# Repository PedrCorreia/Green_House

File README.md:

# LoRaWAN Greenhouse Environmental Monitoring System

**Group 34346** — DTU IoT Project

Distributed IoT system for real-time greenhouse environmental monitoring using LoRa/LoRaWAN wireless communication over ESP32-based sensor nodes.

**Languages & Technologies:** C/C++ | Python | JavaScript | KiCad | Arduino

---

## System Overview

Multi-node greenhouse monitoring network with dual LoRa communication paths.

### Node Architecture
```
5 ESP32-based Nodes:
  • Sensor Node (LoRa P2P telemetry)
  • LoRaWAN Sensor Node (Cibicom OTAA uplink)
  • Gateway (WiFi/MQTT bridge + LoRa P2P RX)
  • Gateway Slave (LoRaWAN serial bridge)
  • Light Control Node (LoRa P2P receiver)
```

### Monitored Parameters
| Parameter | Sensor | Range |
|-----------|--------|-------|
| Temperature & Humidity | DHT22 | -40…+85°C, 0-100% |
| Soil Moisture | Capacitive | 0-100% |
| Light Intensity | KY-018 | 0-4095 lux |
| Battery Voltage | ADC | 0-5000 mV |

### Technology Stack
| Component | Technology |
|-----------|------------|
| Microcontroller | ESP32 DevKit V1 |
| Radio Module | RN2483 LoRa |
| Power Management | AP2112K-3.3 LDO, AO3401A MOSFET |
| PCB Design | KiCad 10.0.0 |
| Communications | LoRa P2P, LoRaWAN (OTAA), WiFi, MQTT |

---

## Firmware Targets

| Target | Language | File | Purpose |
|--------|----------|------|---------|
| Sensor Node | C++ | sensor-node.ino | DHT22/soil/light telemetry over LoRa P2P |
| LoRaWAN Sensor | C++ | lorawan-sensor-node.cpp | OTAA uplink to Cibicom/Loriot |
| Gateway | C++ | gateway.cpp | WiFi/MQTT bridge, LoRa P2P receiver |
| Gateway Slave | C++ | gateway-slave.cpp | LoRaWAN serial bridge |
| Light Node | C++ | light-node.ino | LoRa P2P command receiver for LED control |
| Backend Router | Python | loriot_router.py | 

---

## Communication Architecture

### Primary Path (LoRa P2P)
```
Sensor Node ──LoRa P2P──→ Gateway ──WiFi──→ MQTT Broker ──JSON──→ Dashboard
```

### Secondary Path (LoRaWAN)
```
LoRaWAN Sensor ──LoRaWAN──→ Cibicom/Loriot ──Webhook──→ Router ──MQTT──→ Dashboard
```
---

## Documentation

Individual README files in each directory contain hardware pinouts, configuration details, testing procedures, and troubleshooting.

**References:**
- [RN2483 Datasheet](https://ww1.microchip.com/downloads/en/DeviceDoc/40001811G.pdf)
- [ESP32 Arduino Core](https://github.com/espressif/arduino-esp32)
- [Cibicom LoRaWAN](https://iotnet.teracom.dk)
- [MQTT Protocol](https://mqtt.org)
- [Communication Flowchart](COMMUNICATION_FLOWCHART.md)
- [Hardware Schematics](hardware/)
- [Test Results](test/README.md)

---

**Last Updated:** May 2026 | **Status:** Ready for Submission | **Contact:** Group 34346

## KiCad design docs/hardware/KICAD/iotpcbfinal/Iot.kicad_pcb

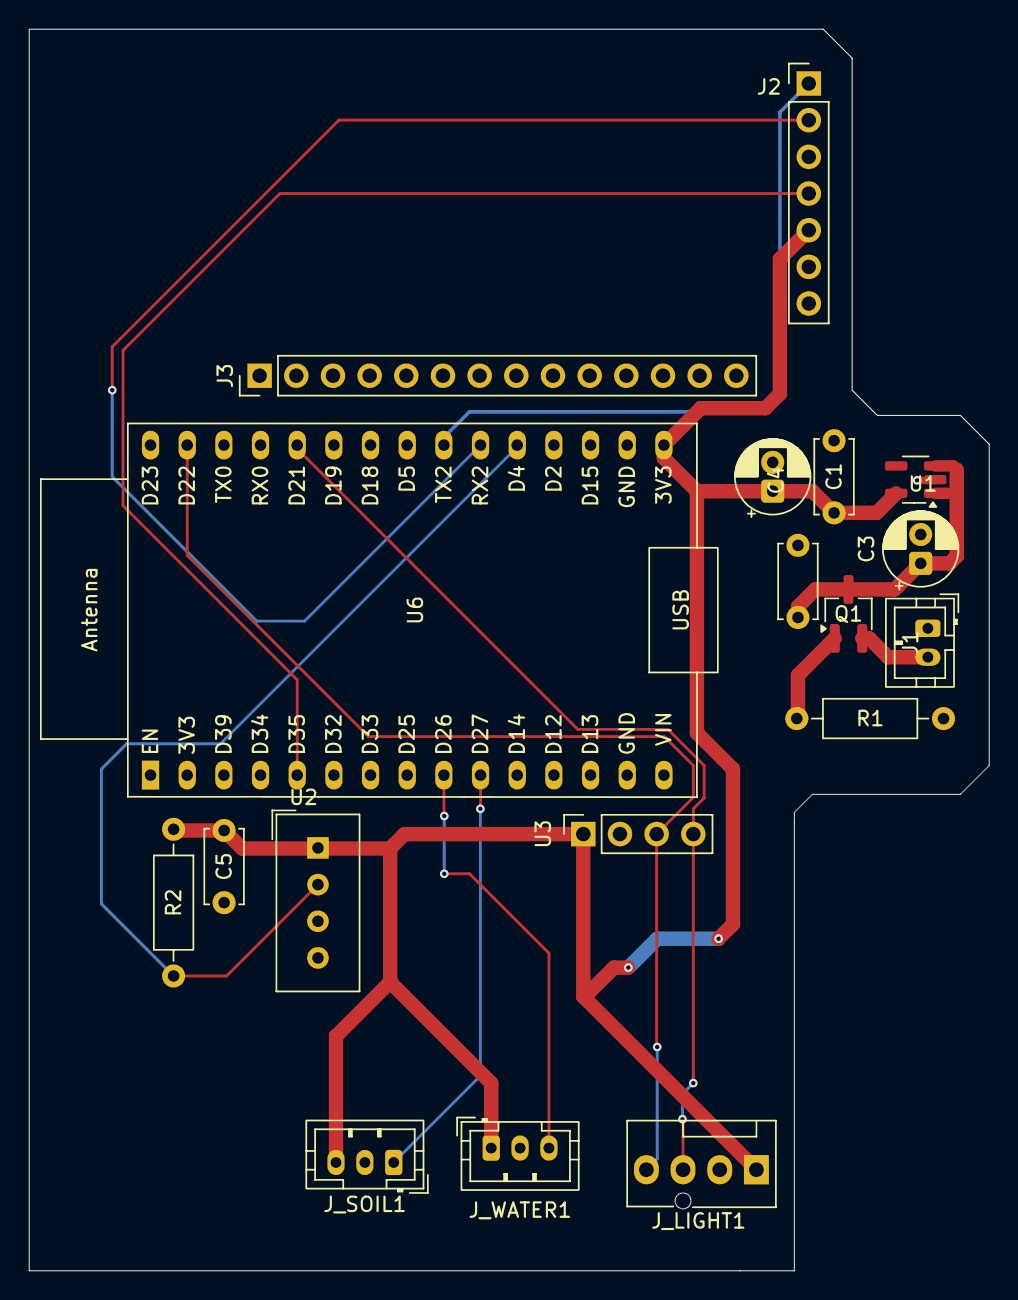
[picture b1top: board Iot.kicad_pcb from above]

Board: 2 copper layers, 66.5 x 86.0 mm, 18 parts (0 on the bottom side), 13 nets.

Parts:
C1, C2: 10uF; C_Disc_D5.0mm_W2.5mm_P5.00mm
C3, C4: 100uF; CP_Radial_D5.0mm_P2.00mm
C5: 100nF; C_Disc_D5.0mm_W2.5mm_P5.00mm
J1: Conn_01x02_Socket; JST_PH_B2B-PH-K_1x02_P2.00mm_Vertical
J2: Conn_01x07_Socket; PinHeader_1x07_P2.54mm_Vertical
J3: Conn_01x14_Socket; PinHeader_1x14_P2.54mm_Vertical
J_LIGHT1: Conn_01x04_Socket; FanPinHeader_1x04_P2.54mm_Vertical
J_SOIL1: Conn_01x03_Socket; JST_PH_B3B-PH-K_1x03_P2.00mm_Vertical
J_WATER1: Conn_01x03_Socket; JST_PH_B3B-PH-K_1x03_P2.00mm_Vertical
Q1: AO3401A; SOT-23W_Handsoldering
R1: 10kΩ; R_Axial_DIN0207_L6.3mm_D2.5mm_P10.16mm_Horizontal
R2: 4.7kΩ; R_Axial_DIN0207_L6.3mm_D2.5mm_P10.16mm_Horizontal
U1: AP2112K-3.3; SOT-23-5_HandSoldering
U2: DHT11; Aosong_DHT11_5.5x12.0_P2.54mm
U3: ER_OLEDM0.91_1x-I2C; PinSocket_1x04_P2.54mm_Vertical
U6: ESP32-C3-DevKitC-02

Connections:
/4.7VIN: J1.2, Q1.2 (S)
/+3V3: C1.1, C4.1, C5.1, J2.5, J_LIGHT1.1, J_SOIL1.3, J_WATER1.1, R2.1, U1.5 (VOUT), U2.1 (VDD), U3.2 (VCC), U6.16 (3.3v)
/I2C_SCL: J_LIGHT1.4, U3.3 (SCL), U6.29 (GPIO22)
/I2C_SDA: J_LIGHT1.3, U3.4 (SDA), U6.26 (GPIO21)
/LORA_RST: J2.4, U6.5 (GPIO14)
/LORA_RX: J2.1, U6.22 (GPIO17)
/LORA_TX: J2.2, U6.21 (GPIO16)
/SOIL_MOIST: J_SOIL1.1, U6.10 (GPIO32)
/TH: R2.2, U2.2 (DATA), U6.20 (GPIO4)
/WATER_LEAK: J_WATER1.3, U6.9 (GPIO33)
Earth: C1.2, C2.2, C3.2, C4.2, C5.2, J1.1, J2.7, J_LIGHT1.2, J_SOIL1.2, J_WATER1.2, R1.2, U1.2 (GND), U2.4 (GND), U3.1 (GND), U6.17 (GND)
unnamed: C2.1, C3.1, Q1.3 (D), U1.1 (VIN), U1.3 (EN)
unnamed: Q1.1 (G), R1.1

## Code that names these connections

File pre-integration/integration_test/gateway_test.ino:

#include <Arduino.h>
#include <HardwareSerial.h>
#include <Wire.h>
#include <Adafruit_GFX.h>
#include <Adafruit_SH110X.h>

// --- LoRa Pins (Matching your Gateway) ---
#define LORA_UART_RX_PIN 16    // ESP32 GPIO16 -> RN2483 TX
#define LORA_UART_TX_PIN 17    // ESP32 GPIO17 -> RN2483 RX
#define RN2483_RST_PIN   2

// --- Display Pins ---
#define I2C_SDA 21
#define I2C_SCL 22

// --- LoRa Settings ---
#define LORA_BAUD_RATE   57600UL
#define LORA_FREQ        868100000UL
#define LORA_PWR         14
#define LORA_SF          "sf12"

// --- Hardware Objects ---
HardwareSerial loraSerial(2);

#define SCREEN_WIDTH 128
#define SCREEN_HEIGHT 64
#define OLED_RESET -1
Adafruit_SH1106G display = Adafruit_SH1106G(SCREEN_WIDTH, SCREEN_HEIGHT, &Wire, OLED_RESET);
bool oled_connected = false;

// Variables to track last received data
String lastRxHex = "";
uint32_t lastId = 0;
float lastTemp = 0.0;
uint8_t lastHum = 0;
uint16_t lastLux = 0;
uint16_t lastSoil = 0;
unsigned long lastRxTime = 0;
int lastRssi = 0; // Signal strength (dBm)

int hexNibble(char c) {
  if (c >= '0' && c <= '9') return c - '0';
  if (c >= 'A' && c <= 'F') return c - 'A' + 10;
  if (c >= 'a' && c <= 'f') return c - 'a' + 10;
  return -1;
}

bool hexToBytes(const String& hexStr, uint8_t* out, size_t outLen) {
  if (hexStr.length() != outLen * 2) return false;
  for (size_t i = 0; i < outLen; i++) {
    int hi = hexNibble(hexStr.charAt(i * 2));
    int lo = hexNibble(hexStr.charAt(i * 2 + 1));
    if (hi < 0 || lo < 0) return false;
    out[i] = (uint8_t)((hi << 4) | lo);
  }
  return true;
}

void parsePayload(String hexStr) {
  if (hexStr.length() != 26) {
    Serial.println("Invalid payload length!");
    return;
  }

  uint8_t b[13];
  if (!hexToBytes(hexStr, b, sizeof(b))) {
    Serial.println("Invalid hex string!");
    return;
  }

  // Parse ID
  lastId = ((uint32_t)b[0] << 24) | ((uint32_t)b[1] << 16) | ((uint32_t)b[2] << 8) | b[3];
  
  // Parse Temp (tenths of C)
  int16_t tempRaw = (int16_t)((b[4] << 8) | b[5]);
  lastTemp = tempRaw / 10.0;

  // Parse Humidity
  lastHum = b[6];

  // Parse Lux
  lastLux = (uint16_t)((b[7] << 8) | b[8]);

  // Parse Soil
  lastSoil = (uint16_t)((b[9] << 8) | b[10]);

  lastRxTime = millis();
}

void updateUI() {
  if (!oled_connected) return;
  display.clearDisplay();
  
  display.setTextSize(1);
  display.setCursor(0, 0);
  display.print("TEST GATEWAY RX");
  display.drawLine(0, 10, 128, 10, SH110X_WHITE);

  if (lastRxTime == 0) {
    display.setCursor(0, 25);
    display.println("Waiting for LoRa...");
  } else {
    display.setCursor(0, 15);
    display.printf("Node ID: %08X", lastId);
    
    display.setCursor(0, 28);
    display.printf("T:%.1fC  H:%d%%", lastTemp, lastHum);
    
    display.setCursor(0, 41);
    display.printf("RSSI: %d dBm", lastRssi);

    // Time since last RX
    unsigned long secAgo = (millis() - lastRxTime) / 1000;
    display.setCursor(0, 54);
    display.printf("Last RX: %ds ago", secAgo);
  }
  
  display.display();
}

void setup() {
  Serial.begin(115200);
  delay(1000);
  Serial.println("\n--- Integration Test: Gateway RX ---");

  // OLED Init
  Wire.begin(I2C_SDA, I2C_SCL);
  if(!display.begin(0x3C, true) && !display.begin(0x3D, true)) {
    Serial.println("WARNING: OLED not found");
  } else {
    oled_connected = true;
    display.clearDisplay();
    display.setTextColor(SH110X_WHITE);
    updateUI();
  }

  // LoRa Init
  pinMode(RN2483_RST_PIN, OUTPUT);
  loraSerial.begin(LORA_BAUD_RATE, SERIAL_8N1, LORA_UART_RX_PIN, LORA_UART_TX_PIN);
  loraSerial.setTimeout(1000);
  
  digitalWrite(RN2483_RST_PIN, LOW);
  delay(200);
  digitalWrite(RN2483_RST_PIN, HIGH);
  delay(500);

  while (loraSerial.available()) loraSerial.read();
  
  loraSerial.print("sys get ver\r\n");
  String ver = loraSerial.readStringUntil('\n');
  ver.trim();
  if (ver.length() > 0) {
    Serial.print("RN2483 Ready: ");
    Serial.println(ver);

    loraSerial.print("mac pause\r\n"); delay(50);
    loraSerial.print("radio set mod lora\r\n"); delay(50);
    loraSerial.print("radio set freq 868100000\r\n"); delay(50);
    loraSerial.print("radio set pwr 14\r\n"); delay(50);
    loraSerial.print("radio set sf sf12\r\n"); delay(50);
    loraSerial.print("radio set afcbw 41.7\r\n"); delay(50);
    loraSerial.print("radio set rxbw 125\r\n"); delay(50);
    loraSerial.print("radio set prlen 8\r\n"); delay(50);
    loraSerial.print("radio set crc on\r\n"); delay(50);
    loraSerial.print("radio set iqi off\r\n"); delay(50);
    loraSerial.print("radio set cr 4/5\r\n"); delay(50);
    loraSerial.print("radio set sync 12\r\n"); delay(50);
    loraSerial.print("radio set bw 125\r\n"); delay(50);
    while (loraSerial.available()) {
       Serial.print((char)loraSerial.read());
    }
    
    // Put radio into continuous RX mode
    loraSerial.print("radio rx 0\r\n");
    Serial.println("Listening on 868.1 MHz for incoming payloads...");
  } else {
    Serial.println("Error: Failed to init LoRa module.");
  }
}

void loop() {
  // Check for incoming LoRa data
  if (loraSerial.available()) {
    String line = loraSerial.readStringUntil('\n');
    line.trim();
    if (line.length() > 0) {
      // Debug: show raw RN2483 output so we can see unexpected responses
      Serial.print("RN2483 raw: ");
      Serial.println(line);
      if (line.startsWith("radio_rx ")) {
        // Handle both formats:
        //  - "radio_rx <payload_hex> <rssi>"
        //  - "radio_rx <payload_hex>"
        String payloadAndMaybeRssi = line.substring(9);
        payloadAndMaybeRssi.trim();
        int sp = payloadAndMaybeRssi.indexOf(' ');
        String hexStr;
        String rssiStr;
        if (sp == -1) {
          hexStr = payloadAndMaybeRssi;
          rssiStr = "";
        } else {
          hexStr = payloadAndMaybeRssi.substring(0, sp);
          rssiStr = payloadAndMaybeRssi.substring(sp + 1);
        }
        hexStr.trim();
        rssiStr.trim();
        if (rssiStr.length() > 0) {
          lastRssi = rssiStr.toInt(); // Parse RSSI value if present
        }
        lastRxHex = hexStr;
        Serial.println("\n[LoRa RX] " + hexStr + " [RSSI: " + (rssiStr.length() ? rssiStr : "n/a") + " dBm]");
        parsePayload(hexStr);
        
        Serial.printf("  => ID   : 0x%08X\n", lastId);
        Serial.printf("  => Temp : %.1f C\n", lastTemp);
        Serial.printf("  => Hum  : %d %%\n", lastHum);
        Serial.printf("  => Lux  : %d lx\n", lastLux);
        Serial.printf("  => Soil : %d\n", lastSoil);

        // Re-enter RX mode after receiving a packet
        loraSerial.print("radio rx 0\r\n"); 
      }
      else if (line == "radio_err") {
        // usually happens if RX mode interrupted or error
        loraSerial.print("radio rx 0\r\n"); 
      }
    }
  }

  // Update UI once a second
  static unsigned long lastUIRefresh = 0;
  if (millis() - lastUIRefresh > 1000) {
    lastUIRefresh = millis();
    updateUI();
  }
}

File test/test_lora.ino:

/*
 * LoRa RN2483 Module Test Script
 * 
 * Hardware:
 * - ESP32
 * - Microchip RN2483A (DrAzzy breakout)
 * 
 * Connections:
 * ESP32 GPIO 16 -> RN2483 RX (UART2 RX)
 * ESP32 GPIO 17 -> RN2483 TX (UART2 TX)
 * ESP32 GPIO 14 -> RN2483 RTS (LORA_RST)
 * 
 * Instructions:
 * 1. Upload this sketch.
 * 2. Open the Serial Monitor at 115200 baud.
 * 3. Ensure both 'Both NL & CR' are selected in the Serial Monitor.
 * 4. The script will boot the RN2483 module and output its version.
 * 5. You can type RN2483 commands (e.g., "sys get ver", "sys get default_env") in the 
 *    Serial Monitor, which will be forwarded to the module, and the response will 
 *    be printed back.
 */

#include <Arduino.h>

#define LORA_RX_PIN 16
#define LORA_TX_PIN 17
#define LORA_RST_PIN 14

// RN2483 Default Baud Rate
#define LORA_BAUD 57600

void setup() {
  // Initialize PC Serial Monitor
  Serial.begin(115200);
  while (!Serial) { ; }
  
  Serial.println("\n--- RN2483 LoRa Module Test ---");

  // Initialize Hardware Serial 2 for the LoRa module
  Serial2.begin(LORA_BAUD, SERIAL_8N1, LORA_RX_PIN, LORA_TX_PIN);

  // Configure Reset Pin
  pinMode(LORA_RST_PIN, OUTPUT);
  
  // Hard reset the RN2483 module
  Serial.println("Resetting LoRa module...");
  digitalWrite(LORA_RST_PIN, LOW);
  delay(100);
  digitalWrite(LORA_RST_PIN, HIGH);
  delay(100);

  Serial.println("Waiting for RN2483 to boot...");
  
  // Wait for the startup message
  delay(500);
  while (Serial2.available()) {
    Serial.write(Serial2.read());
  }

  // Ask for version just in case auto-baud was needed or boot message was missed
  Serial.println("\nSending 'sys get ver'...");
  Serial2.print("sys get ver\r\n");
  delay(100);
  while (Serial2.available()) {
    Serial.write(Serial2.read());
  }

  Serial.println("\n\nReady. Type RN2483 commands and press enter.");
}

void loop() {
  // Read from ESP32 Serial Monitor and send to RN2483
  if (Serial.available()) {
    String command = Serial.readStringUntil('\n');
    command.trim(); // Remove whitespace/newline
    
    if (command.length() > 0) {
      Serial.print("Sending: ");
      Serial.println(command);
      
      // RN2483 commands must be terminated with \r\n
      Serial2.print(command + "\r\n");
    }
  }

  // Read from RN2483 and send to ESP32 Serial Monitor
  if (Serial2.available()) {
    Serial.write(Serial2.read());
  }
}

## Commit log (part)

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2026-04-09 docs: initial PCB documentation structure — IoT Greenhouse Monitor Group 5
2026-04-09 datasheet and images added
2026-04-29 Upload code from drive and comments
2026-04-30 Pipeline integration started
2026-05-01 Documentations and coms plan v0
2026-05-01 plan fix
2026-05-01 fixed coms plan
2026-05-01 fix uneeded py
2026-05-01 updaet type of docs
2026-05-03 added LoRa support, with mock data to show progress
2026-05-04 Add LoRa P2P communication test scripts and README
2026-05-06 did an updated much more refined script, could not test
2026-05-08 Add MQTT LoRa light control test
2026-05-08 Add gateway integration test README
2026-05-08 added gateway integration and sensor node
2026-05-09 Add a more complete failure mechanism
2026-05-11 fix: align transmitter sleep cycle with gateway ping interval
2026-05-11 feat: add shared XOR key to both gateway and transmitter
2026-05-11 docs: add shared key purpose comment to transmitter
2026-05-11 feat: extend PING to include shared key for basic authentication
2026-05-11 feat: transmitter validates PING key, rejects unknown packets
2026-05-11 fix: use long for remaining time, retry on transient RX error in waitForValidPing
2026-05-11 feat: gateway rejects sensor payloads from unapproved device IDs
2026-05-11 feat: XOR-encrypt sensor payload before LoRa transmission
2026-05-11 feat: XOR-decrypt received sensor payload before parsing
2026-05-11 feat: XOR-encrypt light commands gateway to transmitter
2026-05-12 Implement gateway-led sleep sync for LoRa nodes
2026-05-13 chore: ignore docs/superpowers/ directory
2026-05-13 feat: NVS helpers and runtime device list in gateway
2026-05-13 feat: boot button detection for BLE and LoRa pairing modes
2026-05-13 feat: runtime button polling for BLE re-provision
2026-05-13 feat: ESP BLE Provisioning mode with NVS credential storage
2026-05-13 feat: wire setup() to dispatch BLE/pairing/normal modes from NVS
2026-05-13 feat: LoRa pairing mode with REGISTER/ACK protocol
2026-05-13 feat: transmitter registration mode with REGISTER/ACK handshake
2026-05-14 intergration
2026-05-14 pin fix
2026-05-14 pins fixed (magic)
2026-05-14 OLED fix in transmiter
2026-05-15 merged all 3 sub components, kept oled UI, initial sync window and added the schedule
2026-05-15 Restore light control integration
2026-05-18 Added a working lorawan slave
2026-05-18 correct files
2026-05-18 added correct files
2026-05-18 added serial bridge
2026-05-18 added handling of payload from slave
2026-05-18 finally lorawan works
2026-05-18 light control node
2026-05-19 delete the "too dark" data packet
    Prevent automatic light turning on
2026-05-19 new html monitor upload
2026-05-19 git restructure
2026-05-22 update documentation
2026-05-24 Remove obsolete test sketches and main screen UI code for the greenhouse project. This includes the DHT22 test, device ID retrieval, LoRa communication tests, and OLED display tests. The removal stre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
2026-05-24 Kikcad cleanup
2026-05-24 Remove obsolete data packet documentation from README
2026-05-24 fixed history version
